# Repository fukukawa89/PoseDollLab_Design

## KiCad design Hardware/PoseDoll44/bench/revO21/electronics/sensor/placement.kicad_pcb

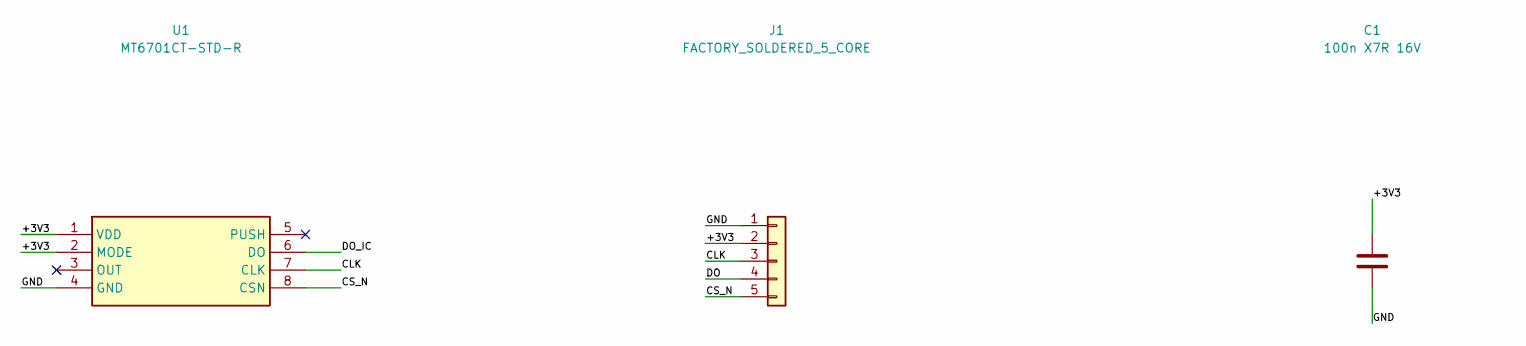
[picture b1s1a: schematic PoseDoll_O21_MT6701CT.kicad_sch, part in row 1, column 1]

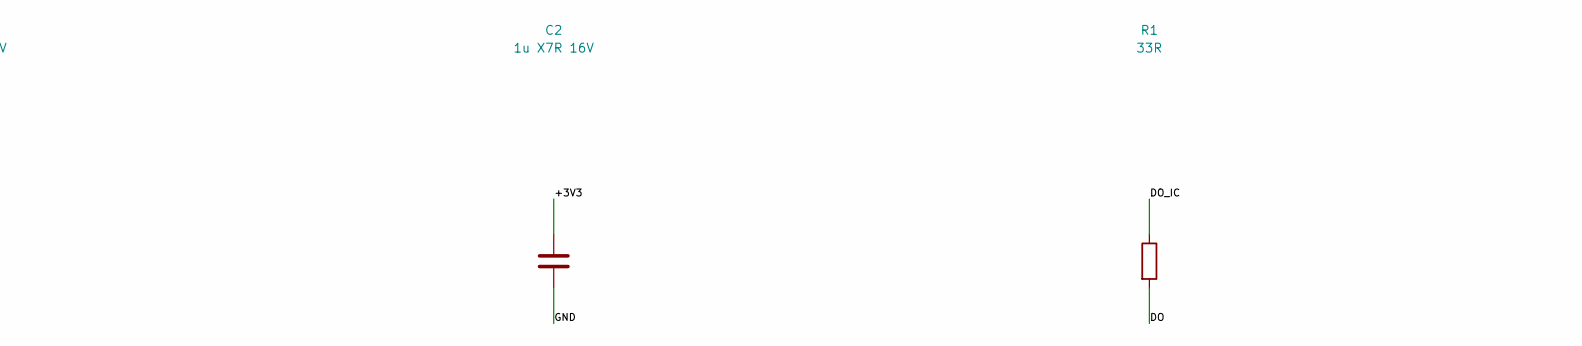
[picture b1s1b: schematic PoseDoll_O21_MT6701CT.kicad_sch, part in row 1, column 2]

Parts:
C1: 100n X7R 16V; C_0603_1608Metric
C2: 1u X7R 16V; C_0603_1608Metric
J1: FACTORY_SOLDERED_5_CORE; WirePads_5P
R1: 33R; R_0603_1608Metric
R2: 10k; R_0603_1608Metric
U1: MT6701CT-STD-R; SOIC-8_3.9x4.9mm_P1.27mm

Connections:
/+3V3: C1.1, C2.1, J1.2, R2.1, U1.1 (VDD), U1.2 (MODE)
/CLK: J1.3, U1.7 (CLK)
/CS_N: J1.5, R2.2, U1.8 (CSN)
/DO: J1.4, R1.2
/DO_IC: R1.1, U1.6 (DO)
/GND: C1.2, C2.2, J1.1, U1.4 (GND)

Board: 2 copper layers, 6 parts (0 on the bottom side), 6 nets, no tracks yet.

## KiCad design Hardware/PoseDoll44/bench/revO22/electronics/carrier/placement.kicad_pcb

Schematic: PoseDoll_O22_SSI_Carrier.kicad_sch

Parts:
C1, C2, C3, C4, C5, C6: 100n; C_0603_1608Metric
C7, C8, C9: 22u 10V X7R effective >=10u; C_0805_2012Metric
C10: 22p C0G starting value; C_0603_1608Metric
D1: SS14 input reverse protection; D_SMA
F4: 1206L110THR / input 1.1A; Fuse_1206_3216Metric
F5: 0467001.NR / 1A fast; Fuse_0603_1608Metric
H1, H2, H3, H4: M2 clearance; MountingHole_2.2mm_M2
J1: XIAO_LEFT D0-D6; PinHeader_1x07_P2.54mm_Vertical
J2: XIAO_RIGHT D7-D10,3V3,GND,5V NC; PinHeader_1x07_P2.54mm_Vertical
J3: EXTERNAL REGULATED 5V ONLY; NO USB VBUS TIE; JST_PH_B2B-PH-SM4-TB_1x02-1MP_P2.00mm_Vertical
J10: A01 BM05B-SRSS-TB; JST_SH_BM05B-SRSS-TB_1x05-1MP_P1.00mm_Vertical
J11: A02 BM05B-SRSS-TB; JST_SH_BM05B-SRSS-TB_1x05-1MP_P1.00mm_Vertical
J12: A03 BM05B-SRSS-TB; JST_SH_BM05B-SRSS-TB_1x05-1MP_P1.00mm_Vertical
J13: A04 BM05B-SRSS-TB; JST_SH_BM05B-SRSS-TB_1x05-1MP_P1.00mm_Vertical
J14: A05 BM05B-SRSS-TB; JST_SH_BM05B-SRSS-TB_1x05-1MP_P1.00mm_Vertical
J15: A06 BM05B-SRSS-TB; JST_SH_BM05B-SRSS-TB_1x05-1MP_P1.00mm_Vertical
J16: A07 BM05B-SRSS-TB; JST_SH_BM05B-SRSS-TB_1x05-1MP_P1.00mm_Vertical
J17: A08 BM05B-SRSS-TB; JST_SH_BM05B-SRSS-TB_1x05-1MP_P1.00mm_Vertical
J18: A09 BM05B-SRSS-TB; JST_SH_BM05B-SRSS-TB_1x05-1MP_P1.00mm_Vertical
J19: A10 BM05B-SRSS-TB; JST_SH_BM05B-SRSS-TB_1x05-1MP_P1.00mm_Vertical
J20: A11 BM05B-SRSS-TB; JST_SH_BM05B-SRSS-TB_1x05-1MP_P1.00mm_Vertical
J21: A12 BM05B-SRSS-TB; JST_SH_BM05B-SRSS-TB_1x05-1MP_P1.00mm_Vertical
J22: A13 BM05B-SRSS-TB; JST_SH_BM05B-SRSS-TB_1x05-1MP_P1.00mm_Vertical
J23: A14 BM05B-SRSS-TB; JST_SH_BM05B-SRSS-TB_1x05-1MP_P1.00mm_Vertical
J26: B01 BM05B-SRSS-TB; JST_SH_BM05B-SRSS-TB_1x05-1MP_P1.00mm_Vertical
J27: B02 BM05B-SRSS-TB; JST_SH_BM05B-SRSS-TB_1x05-1MP_P1.00mm_Vertical
J28: B03 BM05B-SRSS-TB; JST_SH_BM05B-SRSS-TB_1x05-1MP_P1.00mm_Vertical
J29: B04 BM05B-SRSS-TB; JST_SH_BM05B-SRSS-TB_1x05-1MP_P1.00mm_Vertical
J30: B05 BM05B-SRSS-TB; JST_SH_BM05B-SRSS-TB_1x05-1MP_P1.00mm_Vertical
J31: B06 BM05B-SRSS-TB; JST_SH_BM05B-SRSS-TB_1x05-1MP_P1.00mm_Vertical
J32: B07 BM05B-SRSS-TB; JST_SH_BM05B-SRSS-TB_1x05-1MP_P1.00mm_Vertical
J33: B08 BM05B-SRSS-TB; JST_SH_BM05B-SRSS-TB_1x05-1MP_P1.00mm_Vertical
J34: B09 BM05B-SRSS-TB; JST_SH_BM05B-SRSS-TB_1x05-1MP_P1.00mm_Vertical
J35: B10 BM05B-SRSS-TB; JST_SH_BM05B-SRSS-TB_1x05-1MP_P1.00mm_Vertical
J36: B11 BM05B-SRSS-TB; JST_SH_BM05B-SRSS-TB_1x05-1MP_P1.00mm_Vertical
J37: B12 BM05B-SRSS-TB; JST_SH_BM05B-SRSS-TB_1x05-1MP_P1.00mm_Vertical
J38: B13 BM05B-SRSS-TB; JST_SH_BM05B-SRSS-TB_1x05-1MP_P1.00mm_Vertical
J39: B14 BM05B-SRSS-TB; JST_SH_BM05B-SRSS-TB_1x05-1MP_P1.00mm_Vertical
J40: B15 BM05B-SRSS-TB; JST_SH_BM05B-SRSS-TB_1x05-1MP_P1.00mm_Vertical
J41: B16 BM05B-SRSS-TB; JST_SH_BM05B-SRSS-TB_1x05-1MP_P1.00mm_Vertical
J42: C01 BM05B-SRSS-TB; JST_SH_BM05B-SRSS-TB_1x05-1MP_P1.00mm_Vertical
J43: C02 BM05B-SRSS-TB; JST_SH_BM05B-SRSS-TB_1x05-1MP_P1.00mm_Vertical
J44: C03 BM05B-SRSS-TB; JST_SH_BM05B-SRSS-TB_1x05-1MP_P1.00mm_Vertical
J45: C04 BM05B-SRSS-TB; JST_SH_BM05B-SRSS-TB_1x05-1MP_P1.00mm_Vertical
J46: C05 BM05B-SRSS-TB; JST_SH_BM05B-SRSS-TB_1x05-1MP_P1.00mm_Vertical
J47: C06 BM05B-SRSS-TB; JST_SH_BM05B-SRSS-TB_1x05-1MP_P1.00mm_Vertical
J48: C07 BM05B-SRSS-TB; JST_SH_BM05B-SRSS-TB_1x05-1MP_P1.00mm_Vertical
J49: C08 BM05B-SRSS-TB; JST_SH_BM05B-SRSS-TB_1x05-1MP_P1.00mm_Vertical
J50: C09 BM05B-SRSS-TB; JST_SH_BM05B-SRSS-TB_1x05-1MP_P1.00mm_Vertical
J51: C10 BM05B-SRSS-TB; JST_SH_BM05B-SRSS-TB_1x05-1MP_P1.00mm_Vertical
J52: C11 BM05B-SRSS-TB; JST_SH_BM05B-SRSS-TB_1x05-1MP_P1.00mm_Vertical
J53: C12 BM05B-SRSS-TB; JST_SH_BM05B-SRSS-TB_1x05-1MP_P1.00mm_Vertical
J54: C13 BM05B-SRSS-TB; JST_SH_BM05B-SRSS-TB_1x05-1MP_P1.00mm_Vertical
J55: C14 BM05B-SRSS-TB; JST_SH_BM05B-SRSS-TB_1x05-1MP_P1.00mm_Vertical
J56: C15 BM05B-SRSS-TB; JST_SH_BM05B-SRSS-TB_1x05-1MP_P1.00mm_Vertical
J57: C16 BM05B-SRSS-TB; JST_SH_BM05B-SRSS-TB_1x05-1MP_P1.00mm_Vertical
L1: 74438357022 / 2.2uH; L_Wuerth_MAPI-4030
Q1: 2N7002; SOT-23
R1, R10, R11, R12, R13, R14, R15: 100k; R_0603_1608Metric
R2, R40, R41, R42: 10k; R_0603_1608Metric
R30, R31, R32, R33, R34, R35: 33R candidate; R_0603_1608Metric
R50: 316k 0.1%; R_0603_1608Metric
R51: 66.5k 0.1%; R_0603_1608Metric
TP1: GND; TestPoint_Pad_D1.0mm
TP2: REG_3V45; TestPoint_Pad_D1.0mm
TP3: SENSOR_3V45; TestPoint_Pad_D1.0mm
TP4: VIN; TestPoint_Pad_D1.0mm
U1, U2: SN74LVC244APWR; TSSOP-20_4.4x6.5mm_P0.65mm
U3, U4, U5: CD74HC4067PW; TSSOP-24_4.4x7.8mm_P0.65mm
U6: SN74LVC125APWR; TSSOP-14_4.4x5mm_P0.65mm
U7: AP3429AW5-7; TSOT-23-5

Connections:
/A0: U1.5 (Y6), U3.10 (S0), U4.10 (S0), U5.10 (S0)
/A0_MCU: J1.2, R10.1, U1.15 (A6)
/A1: U1.3 (Y7), U3.11 (S1), U4.11 (S1), U5.11 (S1)
/A01_DO: J10.4, U3.9 (I0)
/A1_MCU: J1.4, R11.1, U1.17 (A7)
/A2: U2.18 (Y0), U3.14 (S2), U4.14 (S2), U5.14 (S2)
/A02_DO: J11.4, U3.8 (I1)
/A2_MCU: J1.5, R12.1, U2.2 (A0)
/A3: U2.16 (Y1), U3.13 (S3), U4.13 (S3), U5.13 (S3)
/A03_DO: J12.4, U3.7 (I2)
/A3_MCU: J1.6, R13.1, U2.4 (A1)
/A04_DO: J13.4, U3.6 (I3)
/A05_DO: J14.4, U3.5 (I4)
/A06_DO: J15.4, U3.4 (I5)
/A07_DO: J16.4, U3.3 (I6)
/A08_DO: J17.4, U3.2 (I7)
/A09_DO: J18.4, U3.23 (I8)
/A10_DO: J19.4, U3.22 (I9)
/A11_DO: J20.4, U3.21 (I10)
/A12_DO: J21.4, U3.20 (I11)
/A13_DO: J22.4, U3.19 (I12)
/A14_DO: J23.4, U3.18 (I13)
/B01_DO: J26.4, U4.9 (I0)
/B02_DO: J27.4, U4.8 (I1)
/B03_DO: J28.4, U4.7 (I2)
/B04_DO: J29.4, U4.6 (I3)
/B05_DO: J30.4, U4.5 (I4)
/B06_DO: J31.4, U4.4 (I5)
/B07_DO: J32.4, U4.3 (I6)
/B08_DO: J33.4, U4.2 (I7)
/B09_DO: J34.4, U4.23 (I8)
/B10_DO: J35.4, U4.22 (I9)
/B11_DO: J36.4, U4.21 (I10)
/B12_DO: J37.4, U4.20 (I11)
/B13_DO: J38.4, U4.19 (I12)
/B14_DO: J39.4, U4.18 (I13)
/B15_DO: J40.4, U4.17 (I14)
/B16_DO: J41.4, U4.16 (I15)
/C01_DO: J42.4, U5.9 (I0)
/C02_DO: J43.4, U5.8 (I1)
/C03_DO: J44.4, U5.7 (I2)
/C04_DO: J45.4, U5.6 (I3)
/C05_DO: J46.4, U5.5 (I4)
/C06_DO: J47.4, U5.4 (I5)
/C07_DO: J48.4, U5.3 (I6)
/C08_DO: J49.4, U5.2 (I7)
/C09_DO: J50.4, U5.23 (I8)
/C10_DO: J51.4, U5.22 (I9)
/C11_DO: J52.4, U5.21 (I10)
/C12_DO: J53.4, U5.20 (I11)
/C13_DO: J54.4, U5.19 (I12)
/C14_DO: J55.4, U5.18 (I13)
/C15_DO: J56.4, U5.17 (I14)
/C16_DO: J57.4, U5.16 (I15)
/CLK_A: J10.3, J11.3, J12.3, J13.3, J14.3, J15.3, J16.3, J17.3, J18.3, J19.3, J20.3, J21.3, J22.3, J23.3, R30.2
/CLK_A_DRV: R30.1, U1.18 (Y0)
/CLK_B: J26.3, J27.3, J28.3, J29.3, J30.3, J31.3, J32.3, J33.3, J34.3, J35.3, J36.3, J37.3, J38.3, J39.3, J40.3, J41.3, R32.2
/CLK_B_DRV: R32.1, U1.16 (Y1)
/CLK_C: J42.3, J43.3, J44.3, J45.3, J46.3, J47.3, J48.3, J49.3, J50.3, J51.3, J52.3, J53.3, J54.3, J55.3, J56.3, J57.3, R34.2
/CLK_C_DRV: R34.1, U1.14 (Y2)
/CLK_MCU: J2.2, R14.1, U1.2 (A0), U1.4 (A1), U1.6 (A2)
/CS_A: J10.5, J11.5, J12.5, J13.5, J14.5, J15.5, J16.5, J17.5, J18.5, J19.5, J20.5, J21.5, J22.5, J23.5, R31.2
/CS_A_DRV: R31.1, U1.12 (Y3)
/CS_B: J26.5, J27.5, J28.5, J29.5, J30.5, J31.5, J32.5, J33.5, J34.5, J35.5, J36.5, J37.5, J38.5, J39.5, J40.5, J41.5, R33.2
/CS_B_DRV: R33.1, U1.9 (Y4)
/CS_C: J42.5, J43.5, J44.5, J45.5, J46.5, J47.5, J48.5, J49.5, J50.5, J51.5, J52.5, J53.5, J54.5, J55.5, J56.5, J57.5, R35.2
/CS_C_DRV: R35.1, U1.7 (Y5)
/CS_MCU: J1.7, R15.1, U1.8 (A3), U1.11 (A4), U1.13 (A5)
/DO_A: R40.1, U3.1 (COM), U6.2 (A1)
/DO_A_MCU: J2.3, U6.3 (Y1)
/DO_B: R41.1, U4.1 (COM), U6.5 (A2)
/DO_B_MCU: J2.4, U6.6 (Y2)
/DO_C: R42.1, U5.1 (COM), U6.9 (A3)
/DO_C_MCU: J2.1, U6.8 (Y3)
/ENABLE_N: Q1.3 (D), R2.1, U1.1 (OE1_N), U1.19 (OE2_N), U2.1 (OE1_N), U2.19 (OE2_N), U3.15 (E), U4.15 (E), U5.15 (E)
/EN_MCU: J1.1, Q1.1 (G), R1.1
/EXT5V: F4.1, J3.1
/FB: C10.2, R50.2, R51.1, U7.5 (FB)
/FUSED5V: D1.2 (A), F4.2
/GND: C1.2, C2.2, C3.2, C4.2, C5.2, C6.2, C7.2, C8.2, C9.2, J2.6, J3.2, J10.1, J11.1, J12.1, J13.1, J14.1, J15.1, J16.1, J17.1, J18.1, J19.1, J20.1, J21.1, J22.1, J23.1, J26.1, J27.1, J28.1, J29.1, J30.1, J31.1, J32.1, J33.1, J34.1, J35.1, J36.1, J37.1, J38.1, J39.1, J40.1, J41.1, J42.1, J43.1, J44.1, J45.1, J46.1, J47.1, J48.1, J49.1, J50.1, J51.1, J52.1, J53.1, J54.1, J55.1, J56.1, J57.1, Q1.2 (S), R1.2, R10.2, R11.2, R12.2, R13.2, R14.2, R15.2, R51.2, TP1.1, U1.10 (GND), U2.6 (A2), U2.8 (A3), U2.10 (GND), U2.11 (A4), U2.13 (A5), U2.15 (A6), U2.17 (A7), U3.12 (GND), U3.16 (I15), U3.17 (I14), U4.12 (GND), U5.12 (GND), U6.1 (OE1_N), U6.4 (OE2_N), U6.7 (GND), U6.10 (OE3_N), U6.12 (A4), U7.2 (GND)
/LX: L1.1, U7.3 (LX)
/MCU_3V3: C6.1, J2.5, U6.13 (OE4_N), U6.14 (VCC)
/REG_3V45: C8.1, C9.1, C10.1, F5.1, L1.2, R50.1, TP2.1
/SENSOR_3V45: C1.1, C2.1, C3.1, C4.1, C5.1, F5.2, J10.2, J11.2, J12.2, J13.2, J14.2, J15.2, J16.2, J17.2, J18.2, J19.2, J20.2, J21.2, J22.2, J23.2, J26.2, J27.2, J28.2, J29.2, J30.2, J31.2, J32.2, J33.2, J34.2, J35.2, J36.2, J37.2, J38.2, J39.2, J40.2, J41.2, J42.2, J43.2, J44.2, J45.2, J46.2, J47.2, J48.2, J49.2, J50.2, J51.2, J52.2, J53.2, J54.2, J55.2, J56.2, J57.2, R2.2, R40.2, R41.2, R42.2, TP3.1, U1.20 (VCC), U2.20 (VCC), U3.24 (VCC), U4.24 (VCC), U5.24 (VCC)
/VIN: C7.1, D1.1 (K), TP4.1, U7.1 (EN), U7.4 (VIN)

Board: 2 copper layers, 98 parts (0 on the bottom side), 85 nets, no tracks yet.

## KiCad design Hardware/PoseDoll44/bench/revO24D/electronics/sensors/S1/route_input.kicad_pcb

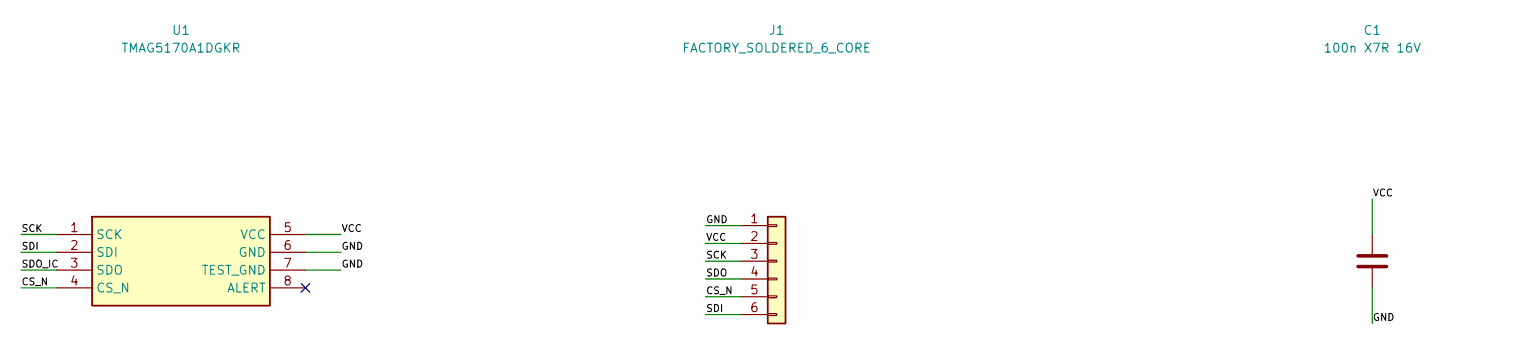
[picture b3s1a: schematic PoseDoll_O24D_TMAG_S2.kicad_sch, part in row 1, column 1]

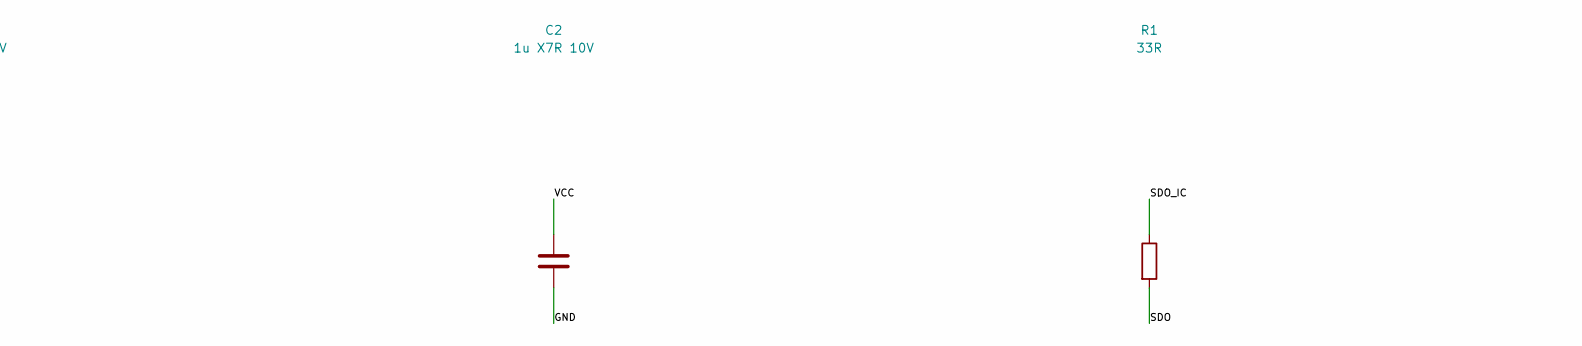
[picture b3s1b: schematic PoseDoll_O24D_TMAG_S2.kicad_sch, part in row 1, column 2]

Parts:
C1: 100n X7R 16V; C_0402_1005Metric
C2: 1u X7R 10V; C_0402_1005Metric
J1: FACTORY_SOLDERED_6_CORE; WirePads_6P
R1: 33R; R_0402_1005Metric
R2: 10k; R_0402_1005Metric
U1: TMAG5170A1DGKR; VSSOP-8_3x3mm_P0.65mm

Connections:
/CS_N: J1.5, R2.2, U1.4 (CS_N)
/GND: C1.2, C2.2, J1.1, U1.6 (GND), U1.7 (TEST_GND)
/SCK: J1.3, U1.1 (SCK)
/SDI: J1.6, U1.2 (SDI)
/SDO: J1.4, R1.2
/SDO_IC: R1.1, U1.3 (SDO)
/VCC: C1.1, C2.1, J1.2, R2.1, U1.5 (VCC)

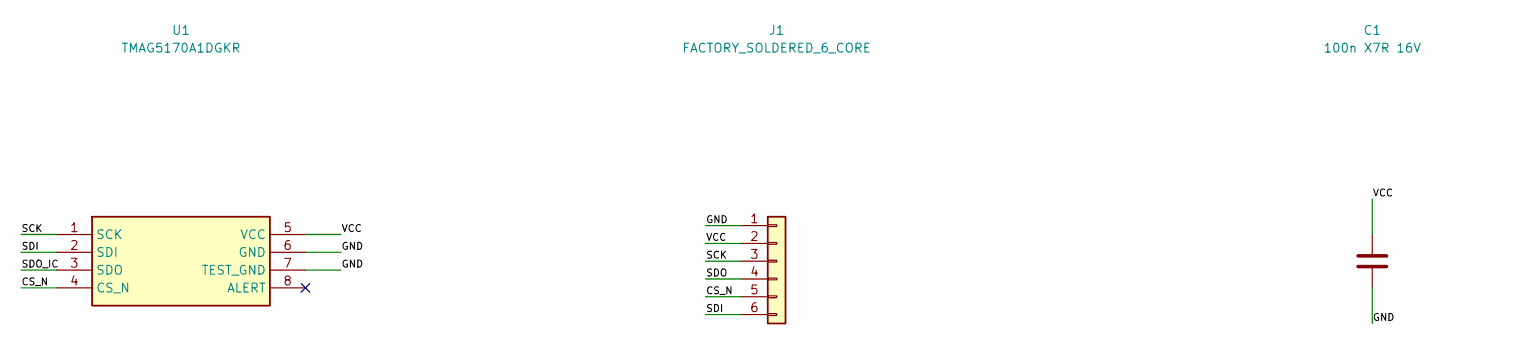
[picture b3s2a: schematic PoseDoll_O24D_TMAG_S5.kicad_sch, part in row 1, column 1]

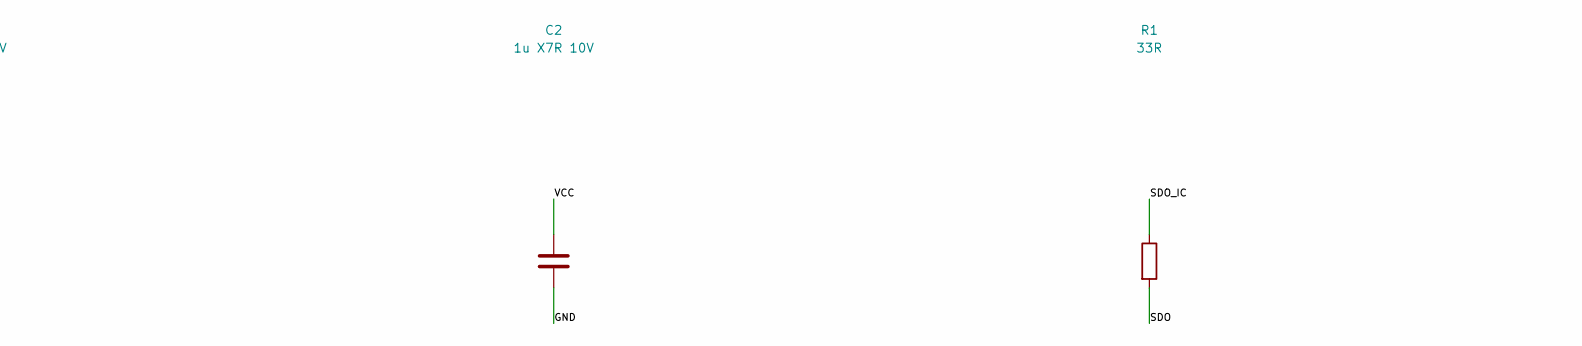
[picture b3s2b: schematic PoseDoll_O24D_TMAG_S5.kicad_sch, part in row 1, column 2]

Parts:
C1: 100n X7R 16V; C_0402_1005Metric
C2: 1u X7R 10V; C_0402_1005Metric
J1: FACTORY_SOLDERED_6_CORE; WirePads_6P
R1: 33R; R_0402_1005Metric
R2: 10k; R_0402_1005Metric
U1: TMAG5170A1DGKR; VSSOP-8_3x3mm_P0.65mm

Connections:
/CS_N: J1.5, R2.2, U1.4 (CS_N)
/GND: C1.2, C2.2, J1.1, U1.6 (GND), U1.7 (TEST_GND)
/SCK: J1.3, U1.1 (SCK)
/SDI: J1.6, U1.2 (SDI)
/SDO: J1.4, R1.2
/SDO_IC: R1.1, U1.3 (SDO)
/VCC: C1.1, C2.1, J1.2, R2.1, U1.5 (VCC)

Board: 2 copper layers, 6 parts (0 on the bottom side), 7 nets, no tracks yet.
